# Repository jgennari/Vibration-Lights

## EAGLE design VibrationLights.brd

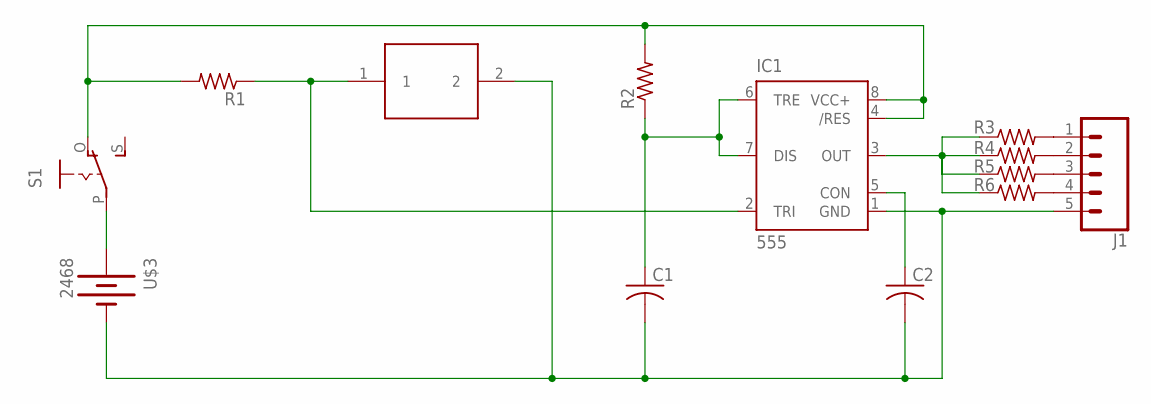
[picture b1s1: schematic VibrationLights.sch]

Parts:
C1: C-US050-045X075; C050-045X075
C2: C-US025-050X050; C025-050X050
IC1: 555; DIP08
J1: CONN_05PTH_LONGPADS; 1X05_LONGPADS
R1, R2, R3, R4, R5, R6: R-US_0204/5; 0204/5
S1: EG1218S; EG1218
U$1: SW-18010P
U$3: 2468

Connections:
GND: C1.2, C2.2, IC1.1 (GND), J1.5, U$1.2, U$3.NEG (-)
unnamed: C1.1, IC1.6 (TRE), IC1.7 (DIS), R2.1
unnamed: J1.1, R3.2
unnamed: IC1.2 (TRI), R1.1, U$1.1
unnamed: J1.2, R4.2
unnamed: C2.1, IC1.5 (CON)
unnamed: J1.3, R5.2
unnamed: J1.4, R6.2
unnamed: IC1.3 (OUT), R3.1, R4.1, R5.1, R6.1
unnamed: S1.P, U$3.POS (+)
VCC: IC1.4 (/RES), IC1.8 (VCC+), R1.2, R2.2, S1.O

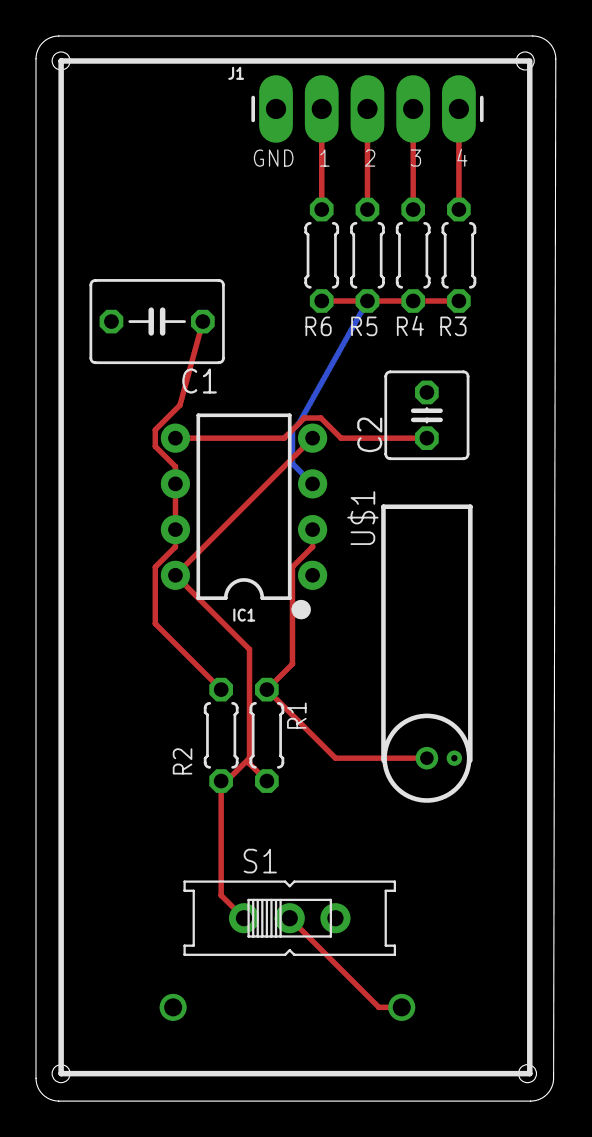
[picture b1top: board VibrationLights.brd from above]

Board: 2 copper layers, 28.9 x 59.2 mm, 13 parts (1 on the bottom side), 11 nets.

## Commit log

2017-12-18 Added files
2017-12-18 Remove ignored files

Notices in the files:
parts and their libraries:
SparkFun-IC-Special-Function: Licensing: Creative Commons ShareAlike 4.0 International - https://creativecommons.org/licenses/by-sa/4.0
